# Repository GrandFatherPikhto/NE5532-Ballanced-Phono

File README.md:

# NE5532 Balanced Phono Preamplifier

[Русская версия](README_ru.md)

A stereo moving-magnet phono preamplifier for the Audio-Technica AT-3600L,
using NE5532 operational amplifiers and RIAA playback equalization.
The main design has balanced inputs from floating cartridge coils and
conventional, ground-referenced line outputs. An earlier unbalanced design
is retained for comparison.

## Design

Each channel uses two input amplifiers with a shared gain-setting bridge,
followed by a differential amplifier with the 75 µs RIAA pole. The stereo
design uses three dual NE5532 packages and a ±12 V supply.

| Parameter | Nominal design |
| --- | --- |
| Cartridge | Audio-Technica AT-3600L, moving magnet |
| Differential input load | 47 kΩ in the midband: 23.5 kΩ from each input to GND |
| Input coupling | 4.7 µF per leg |
| Input amplifier feedback | 90.9 kΩ in parallel with a series 10 kΩ / 31.5 nF branch |
| Gain bridge | 182 Ω in series with two back-to-back 1000 µF capacitors |
| Differential amplifier | Four 10 kΩ resistors and two matched 7.5 nF capacitors per channel |
| Line output | 100 Ω, series 4.7 µF, 100 kΩ to GND |
| Power | ±12 V, supplied through J3 |

The bridge capacitors have their negative terminals joined at a floating
midpoint. Their linear series equivalent is 500 µF. The L− and R− cartridge
connections remain separate from GND; cable shields and the tonearm ground
are separate connections.

With the nominal values in `scripts/config.toml` and an external 47 kΩ load,
the ideal model gives 100.723 V/V (40.063 dB) at 1 kHz. A 4 mV RMS
differential input gives approximately 0.403 V RMS at that frequency.
The ideal RIAA deviation, normalized at 1 kHz, is −0.0683 to +0.0018 dB
over 20 Hz–20 kHz.

## Project status and model limits

PCB routing is complete; hardware measurements are still pending. Component
ratings and purchased parts must be checked before assembly.
The separate LM317/LM337 power supply is documented in
LaTeX; the KiCad preamplifier schematic receives regulated ±12 V and does
not include that regulator circuit.

The Python tools compare an analytical transfer function with a nodal model
and estimate the effect of a single-pole op-amp model. These calculations
do not establish measured noise, THD, stability, overload margin or CMRR.
They omit cartridge impedance, cable capacitance, component tolerances,
capacitor leakage and nonlinearity, and PCB parasitics.

## Files

| Path | Contents |
| --- | --- |
| `PreAmp.kicad_pro`, `PreAmp.kicad_sch` | Main KiCad project and schematic |
| `channel.kicad_sch`, `arm.kicad_sch`, `power.kicad_sch` | Active hierarchical sheets; earlier variants are kept separately |
| `PreAmp.net` | Exported netlist snapshot; may lag behind the schematic |
| `out/` | Condensed netlists, BOM and audit snapshots for quick inspection |
| `scripts/` | Python models, plotting tools, dependencies and `config.toml` |
| `docs/latex/` | Circuit documents, shared LaTeX support files and PDF snapshots |
| `docs/images/` | Published simulation plots in PNG, SVG and PDF |
| [docs/simulation/ngspice-2026-11-28/](docs/simulation/ngspice-2026-11-28/) | Archived ngspice results, source netlists and run parameters |
| [docs/PHONO_GUIDE.pdf](docs/PHONO_GUIDE.pdf) | Detailed design guide in Russian; source: [PHONO_GUIDE.tex](docs/PHONO_GUIDE.tex) |
| [docs/POWER.md](docs/POWER.md) | Preliminary transformer notes; actual voltages and phasing require verification |
| `docs/scheme/` | Reference scans for the Melodiya-103 player |
| `build/` | Generated calculations, plots, check reports and document builds; ignored by Git |

Use the current KiCad schematic to establish connectivity and
`scripts/config.toml` for the calculation parameters. KiCad, TOML and LaTeX
are maintained independently; changing one does not update the others.
Historical filenames containing `ballanced` and `ad3600l` are preserved.

## Run the calculations

Use Python 3.11 or newer. Run these commands from the repository root:

```sh
python3 -m venv scripts/.venv
scripts/.venv/bin/python -m pip install -e scripts
scripts/.venv/bin/python scripts/calculate_balanced_riaa.py
scripts/.venv/bin/python scripts/calculate_unbalanced_riaa.py
scripts/.venv/bin/python scripts/render_phono_guide.py
```

Dependencies are declared in `scripts/pyproject.toml`. Both calculation
scripts load `scripts/config.toml` by default and write CSV, JSON, PNG and
PDF results to `build/balanced_riaa/`, including the unbalanced results.
The guide renderer writes to `build/phono_guide/`.

To choose a configuration and output directory explicitly:

```sh
scripts/.venv/bin/python scripts/calculate_balanced_riaa.py \
  --config scripts/config.toml --output-dir build/check
```

## Run the QSPICE simulation on Windows

Install Python 3.11 or later, KiCad with `kicad-cli.exe`, and QSPICE with
`QSPICE64.exe`. Open PowerShell in the project root and run:

```powershell
python -m pip install -e scripts
python scripts/simulate_qspice.py
```

Install the Python dependencies once per environment. Save your changes in
KiCad before each run. The script exports the saved hierarchical schematic
`PreAmp.kicad_sch` to fresh XML and builds the SPICE netlists from that export.
Component values and connections come from this XML, so there is no need to
regenerate `PreAmp.net`.

The [`[qspice]` section of the TOML file](scripts/config.toml) controls the
output directory, report and plot generation, and optional overrides for
frequency range, point count, RIAA reference frequency, and external load.
Set `kicad_cli` and `qspice64` there if automatic detection misses your
installation, or pass `--kicad-cli` and `--qspice64` on the command line.
Use `--config path/to/config.toml` for a separate set of settings. Setting
`write_plots = false` allows running without Matplotlib.

Each run prints the path to its results directory (by default,
`build/qspice/run-*/`). Open `report.md` for gain at the reference frequency
and the RIAA error extrema and their frequencies. Open `response.png` or
`response.svg` for both channels' gain, phase, and RIAA error. The directory
also contains per-channel CSV, CIR and QRAW files and the KiCad XML export.

The script generates a linear, single-pole NE5532 approximation from the
existing `[opamp]` settings (default open-loop gain 100,000 and GBW 12 MHz).
It estimates gain and phase with an ideal differential source. Cartridge
impedance, cable capacitance, noise, and output clipping are outside this
model.

## Run ngspice independently

Install ngspice and KiCad CLI, then run from the project root:

```sh
python scripts/simulate_ngspice.py
```

This exports the saved KiCad schematic and runs both channels without a
previous QSPICE run. On Linux and Windows, native ngspice is used when found
on `PATH`. On Windows, `backend = "auto"` falls back to ngspice inside WSL;
KiCad CLI still runs on the host. Use `--backend native` or `--backend wsl`
to select explicitly.

The [`[ngspice]` section](scripts/config.toml) controls the backend, output
directory, report/plot switches, timeout and optional overrides of the
`[analysis]` frequency range, reference frequency, load and point count.
`points` controls the target logarithmic sweep density; the exact sample
count can differ because SPICE uses an integer number of points per decade.
Executable paths can be set with `ngspice`/`kicad_cli` or the CLI options
`--ngspice`/`--kicad-cli`. `wsl_distro` or `--distro` selects the WSL distribution.
CLI options take priority. Paths in TOML are relative to the project root;
an executable's bare name is looked up on `PATH`.

```sh
python scripts/simulate_ngspice.py --config scripts/config.toml --backend native
python scripts/compare_ngspice.py build/qspice/run-example --backend native
```

Results go to a new `build/ngspice/run-*/` directory: per-channel CSV
(gain, phase and RIAA error), DAT (frequency and complex voltage), CIR and
logs, plus the KiCad XML, original configuration and effective run metadata.
With `write_report = true`, `report.md` and `report.json` contain the gain
and RIAA extrema; with `write_plots = true`, `response.png` and `response.svg`
show gain, phase and RIAA error for both channels. Disable plots to run
without Matplotlib. Comparison mode retains its per-channel comparison CSV
and uses the same ngspice backend settings without modifying the QSPICE decks.

Both simulators use the same linear one-pole op-amp approximation described
above. These plots do not predict noise, distortion, overload or real-device
stability.

## Published ngspice results — 28 November 2026

The snapshot below comes from `build/ngspice/run-_ttt3q4u`, using ngspice
45.2 with the KiCad-exported component values and connections. The input is
an ideal differential source; the external load is 47 kΩ per channel.
The sweep covers 20 Hz–20 kHz with 1003 samples per channel. RIAA deviation
is normalized at 1 kHz. The one-pole op-amp model uses A₀ = 100,000 and
GBW = 12 MHz.

| Quantity | Left | Right |
| --- | ---: | ---: |
| Gain at 1 kHz, V/V | 100.23888 | 100.23888 |
| Gain at 1 kHz, dB | 40.02072 | 40.02072 |
| Minimum RIAA deviation, dB | −0.11942 at 20 kHz | −0.11942 at 20 kHz |
| Maximum RIAA deviation, dB | +0.00131 at 382.36 Hz | +0.00131 at 382.36 Hz |

The top panel shows the intended RIAA playback response; the falling gain
with frequency is part of the equalization. The middle panel shows signal
phase, and the bottom panel shows deviation from the RIAA reference after
removing the gain difference at 1 kHz. For a 4 mV RMS differential input,
the modeled output at 1 kHz is approximately 0.401 V RMS.

The L/R curves overlap because the simulation uses matched nominal parts
and identical op-amp parameters, without component tolerances. This does
not establish real channel matching or CMRR. The finite open-loop gain
makes this result slightly different from the ideal-op-amp calculation
above. The KiCad snapshot also uses 23.51 kΩ and 90.91 kΩ resistor sums,
where the analytical configuration uses rounded 23.5 kΩ and 90.9 kΩ values.
Cartridge/cable impedance, PCB parasitics, noise, distortion, clipping and
real-device stability are outside this model.

The [archived data and reproduction notes](docs/simulation/ngspice-2026-11-28/README.md)
include CSV/DAT results, SPICE decks, the KiCad XML, configuration and run
metadata. The [balanced circuit PDF](docs/latex/ne5532_ad3600l_ballanced.pdf)
and [design guide](docs/PHONO_GUIDE.pdf) include the same results and comments.

## Build the documents

Install XeLaTeX, latexmk and the TeX packages used by the documents, including
TikZ/PGFPlots, fontspec and polyglossia. The shared preamble requires
Times New Roman, Arial and Courier New. A local circuitikz style is included.
Generate the calculations and guide figures above before building.

From the repository root:

```sh
TEXINPUTS=.:./docs/latex//: latexmk -xelatex -interaction=nonstopmode \
  -halt-on-error -outdir=build/latex docs/latex/ne5532_ad3600l_ballanced.tex
TEXINPUTS=.:./docs/latex//: latexmk -xelatex -interaction=nonstopmode \
  -halt-on-error -outdir=build/latex docs/latex/ne5532_at3600l.tex
TEXINPUTS=.:./docs/latex//: latexmk -xelatex -interaction=nonstopmode \
  -halt-on-error -outdir=build/latex docs/latex/analog_power_lm317_lm337.tex
TEXINPUTS=.:./docs/latex//: latexmk -xelatex -interaction=nonstopmode \
  -halt-on-error -outdir=build/phono_guide docs/PHONO_GUIDE.tex
```

The trailing colon in `TEXINPUTS` preserves the system TeX search path.
New PDFs remain in `build/`; checked-in PDF snapshots under `docs/` are
updated manually. Some existing documents contain commands from an earlier
directory layout; use the commands in this README for the current layout.

## Check the KiCad schematic

The project was last checked with KiCad 10.0.8. Save changes in the editor
before exporting or running ERC:

```sh
mkdir -p build/review
kicad-cli sch erc --format json --severity-all \
  --output build/review/erc.json PreAmp.kicad_sch
kicad-cli sch export netlist --format kicadsexpr \
  --output build/review/PreAmp.net PreAmp.kicad_sch
```

ERC checks enabled electrical rules. It does not validate component ratings,
footprint dimensions, equalization accuracy, stability or PCB layout.

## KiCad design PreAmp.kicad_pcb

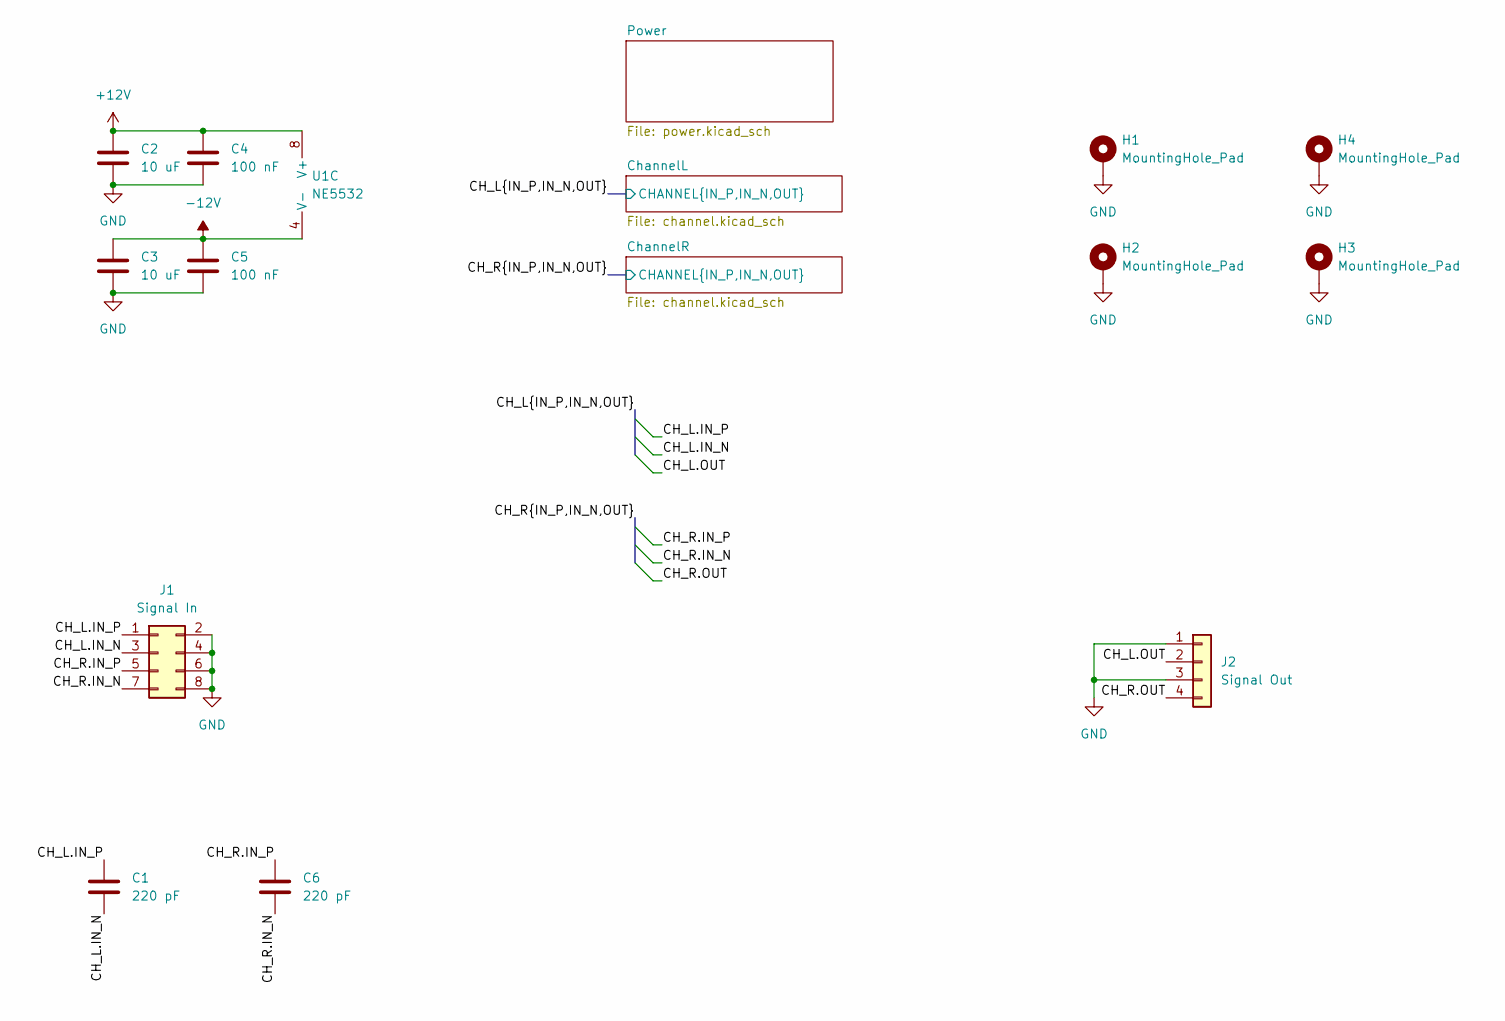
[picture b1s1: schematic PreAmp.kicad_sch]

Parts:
C1, C6: 220 pF; C_0603_1608Metric_Pad1.08x0.95mm_HandSolder
C2, C3: 10 uF; C_0603_1608Metric_Pad1.08x0.95mm_HandSolder
C4, C5: 100 nF; C_0402_1005Metric_Pad0.74x0.62mm_HandSolder
H1, H2, H3, H4: MountingHole_Pad; MountingHole_3.2mm_M3_DIN965_Pad
J1: Signal In; IDC-Header_2x04_P2.54mm_Vertical
J2: Signal Out; JST_XH_B4B-XH-A_1x04_P2.50mm_Vertical
U1: NE5532; SOIC-8_3.9x4.9mm_P1.27mm

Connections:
+12V: C2.1, C4.1, U1.8 (V+); also elsewhere on the board
-12V: C3.1, C5.1, U1.4 (V-); also elsewhere on the board
/CH_L.IN_N: C1.2, J1.3; also elsewhere on the board
/CH_L.IN_P: C1.1, J1.1; also elsewhere on the board
/CH_L.OUT: J2.2; also elsewhere on the board
/CH_R.IN_N: C6.2, J1.7; also elsewhere on the board
/CH_R.IN_P: C6.1, J1.5; also elsewhere on the board
/CH_R.OUT: J2.4; also elsewhere on the board
/ChannelR/DIFF_IN_N: U1.6 (-); also elsewhere on the board
/ChannelR/DIFF_IN_P: U1.5 (+); also elsewhere on the board
/ChannelR/DIFF_OUT: U1.7; also elsewhere on the board
GND: C2.2, C3.2, C4.2, C5.2, H1.1 (1_1), H2.1 (1_1), H3.1 (1_1), H4.1 (1_1), J1.2, J1.4, J1.6, J1.8, J2.1, J2.3; also elsewhere on the board

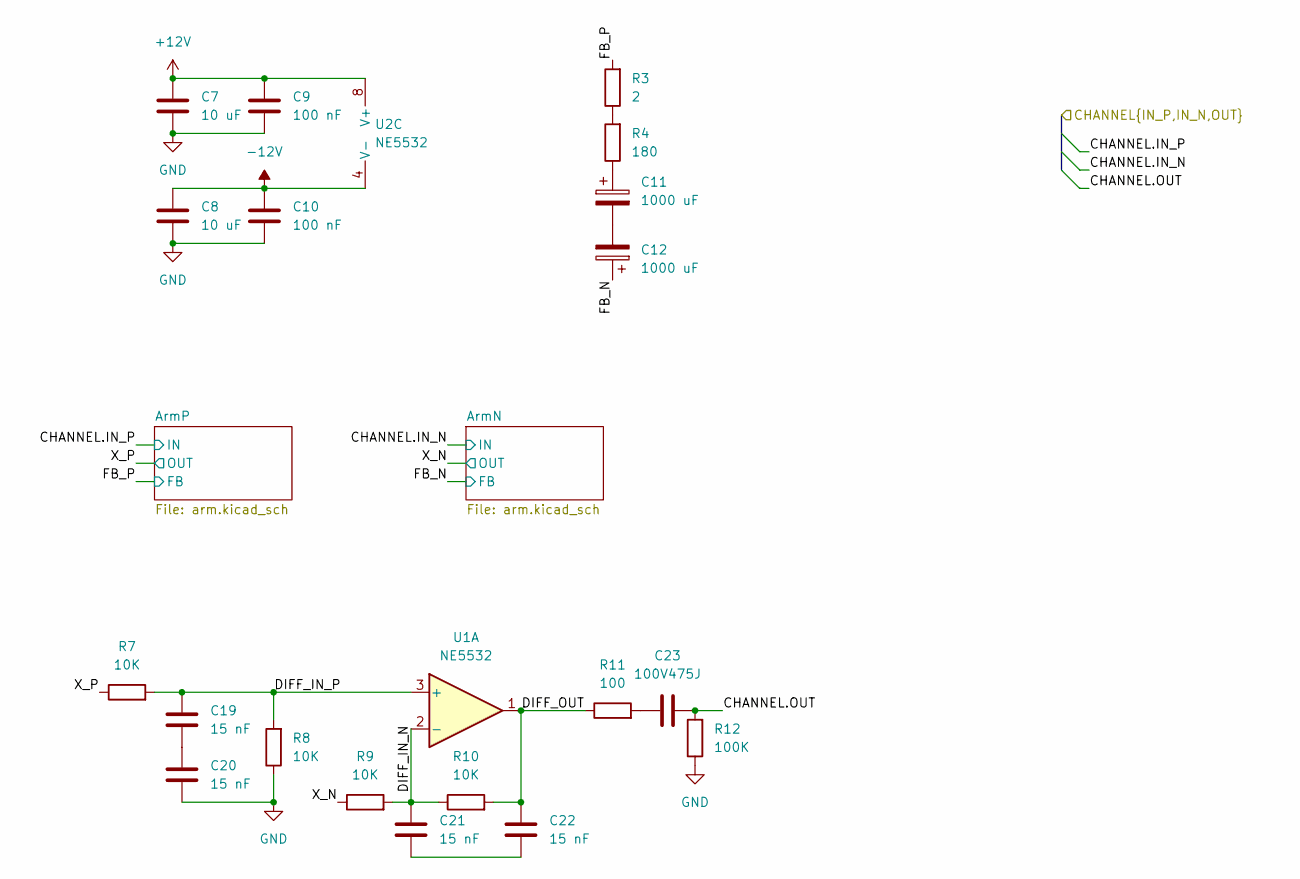
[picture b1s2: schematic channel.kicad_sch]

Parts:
C7, C8: 10 uF; C_0603_1608Metric_Pad1.08x0.95mm_HandSolder
C9, C10: 100 nF; C_0402_1005Metric_Pad0.74x0.62mm_HandSolder
C11, C12: 1000 uF; CP_Radial_D10.0mm_P5.00mm
C19, C20, C21, C22: 15 nF; C_0603_1608Metric_Pad1.08x0.95mm_HandSolder
C23: 100V475J; C_Rect_L18.0mm_W8.0mm_P15.00mm_FKS3_FKP3
R3: 2; R_0603_1608Metric_Pad0.98x0.95mm_HandSolder
R4: 180; R_0603_1608Metric_Pad0.98x0.95mm_HandSolder
R7, R8, R9, R10: 10K; R_0402_1005Metric_Pad0.72x0.64mm_HandSolder
R11: 100; R_0402_1005Metric_Pad0.72x0.64mm_HandSolder
R12: 100K; R_0402_1005Metric_Pad0.72x0.64mm_HandSolder
U1, U2: NE5532; SOIC-8_3.9x4.9mm_P1.27mm

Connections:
+12V: C7.1, C9.1, U2.8 (V+); also elsewhere on the board
-12V: C8.1, C10.1, U2.4 (V-); also elsewhere on the board
/CH_L.OUT: C23.2, R12.2; also elsewhere on the board
/ChannelL/ArmN/IN_AC: U2.5 (+); also elsewhere on the board
/ChannelL/DIFF_IN_N: C21.2, R9.2, R10.1, U1.2 (-)
/ChannelL/DIFF_IN_P: C19.1, R7.2, R8.2, U1.3 (+)
/ChannelL/DIFF_OUT: C22.1, R10.2, R11.1, U1.1
/ChannelL/FB_N: C12.1, U2.6 (-); also elsewhere on the board
/ChannelL/FB_P: R3.2; also elsewhere on the board
/ChannelL/X_N: R9.1, U2.7; also elsewhere on the board
/ChannelL/X_P: R7.1; also elsewhere on the board
/ChannelR/DIFF_IN_N: U1.6 (-); also elsewhere on the board
/ChannelR/DIFF_IN_P: U1.5 (+); also elsewhere on the board
/ChannelR/DIFF_OUT: U1.7; also elsewhere on the board
GND: C7.2, C8.2, C9.2, C10.2, C20.2, R8.1, R12.1; also elsewhere on the board
unnamed: C11.1, R4.1
unnamed: C11.2, C12.2
unnamed: C19.2, C20.1
unnamed: C21.1, C22.2
unnamed: C23.1, R11.2
unnamed: R3.1, R4.2

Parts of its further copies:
C13, C14: 10 uF; C_0603_1608Metric_Pad1.08x0.95mm_HandSolder
C15, C16: 100 nF; C_0402_1005Metric_Pad0.74x0.62mm_HandSolder
C17, C18: 1000 uF; CP_Radial_D10.0mm_P5.00mm
C24, C25, C26, C27: 15 nF; C_0603_1608Metric_Pad1.08x0.95mm_HandSolder
C28: 100V475J; C_Rect_L18.0mm_W8.0mm_P15.00mm_FKS3_FKP3
R5: 2; R_0603_1608Metric_Pad0.98x0.95mm_HandSolder
R6: 180; R_0603_1608Metric_Pad0.98x0.95mm_HandSolder
R13, R14, R15, R16: 10K; R_0402_1005Metric_Pad0.72x0.64mm_HandSolder
R17: 100; R_0402_1005Metric_Pad0.72x0.64mm_HandSolder
R18: 100K; R_0402_1005Metric_Pad0.72x0.64mm_HandSolder
U3: NE5532; SOIC-8_3.9x4.9mm_P1.27mm

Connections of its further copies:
+12V: C13.1, C15.1, U3.8 (V+); also elsewhere on the board
-12V: C14.1, C16.1, U3.4 (V-); also elsewhere on the board
/CH_R.OUT: C28.2, R18.2; also elsewhere on the board
/ChannelR/ArmN/IN_AC: U3.5 (+); also elsewhere on the board
/ChannelR/ArmP/IN_AC: U3.3 (+); also elsewhere on the board
/ChannelR/DIFF_IN_N: C26.2, R15.2, R16.1; also elsewhere on the board
/ChannelR/DIFF_IN_P: C24.1, R13.2, R14.2; also elsewhere on the board
/ChannelR/DIFF_OUT: C27.1, R16.2, R17.1; also elsewhere on the board
/ChannelR/FB_N: C18.1, U3.6 (-); also elsewhere on the board
/ChannelR/FB_P: R5.2, U3.2 (-); also elsewhere on the board
/ChannelR/X_N: R15.1, U3.7; also elsewhere on the board
/ChannelR/X_P: R13.1, U3.1; also elsewhere on the board
GND: C13.2, C14.2, C15.2, C16.2, C25.2, R14.1, R18.1; also elsewhere on the board
unnamed: C17.1, R6.1
unnamed: C17.2, C18.2
unnamed: C24.2, C25.1
unnamed: C26.1, C27.2
unnamed: C28.1, R17.2
unnamed: R5.1, R6.2

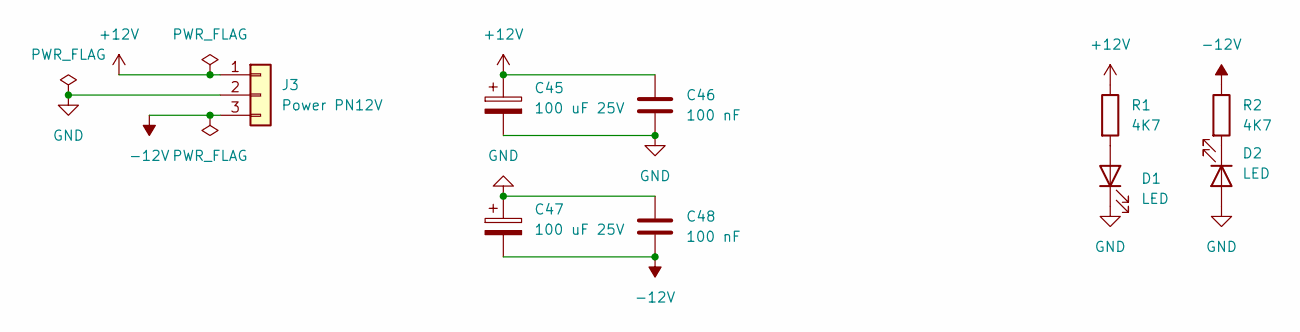
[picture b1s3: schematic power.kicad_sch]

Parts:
C45, C47: 100 uF 25V; CP_Radial_D5.0mm_P2.50mm
C46, C48: 100 nF; C_0603_1608Metric_Pad1.08x0.95mm_HandSolder
D1, D2: LED; LED_0805_2012Metric_Pad1.15x1.40mm_HandSolder
J3: Power PN12V; JST_XH_B3B-XH-A_1x03_P2.50mm_Vertical
R1, R2: 4K7; R_0603_1608Metric_Pad0.98x0.95mm_HandSolder

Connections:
+12V: C45.1, C46.1, J3.1, R1.1; also elsewhere on the board
-12V: C47.2, C48.2, J3.3, R2.1; also elsewhere on the board
GND: C45.2, C46.2, C47.1, C48.1, D1.1 (K), D2.2 (A), J3.2; also elsewhere on the board
unnamed: D1.2 (A), R1.2
unnamed: D2.1 (K), R2.2

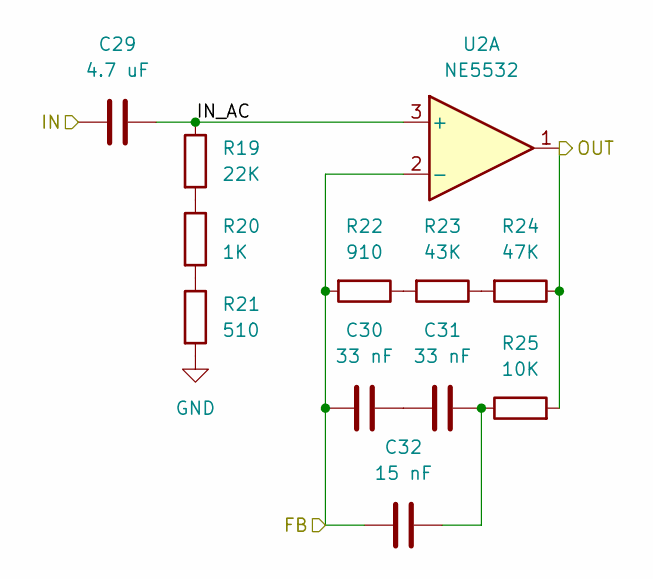
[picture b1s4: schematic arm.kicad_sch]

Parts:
C29: 4.7 uF; C_Rect_L18.0mm_W8.0mm_P15.00mm_FKS3_FKP3
C30, C31: 33 nF; C_0603_1608Metric_Pad1.08x0.95mm_HandSolder
C32: 15 nF; C_0603_1608Metric_Pad1.08x0.95mm_HandSolder
R19: 22K; R_0402_1005Metric_Pad0.72x0.64mm_HandSolder
R20: 1K; R_0402_1005Metric_Pad0.72x0.64mm_HandSolder
R21: 510; R_0402_1005Metric_Pad0.72x0.64mm_HandSolder
R22: 910; R_0402_1005Metric_Pad0.72x0.64mm_HandSolder
R23: 43K; R_0402_1005Metric_Pad0.72x0.64mm_HandSolder
R24: 47K; R_0402_1005Metric_Pad0.72x0.64mm_HandSolder
R25: 10K; R_0402_1005Metric_Pad0.72x0.64mm_HandSolder
U2: NE5532; SOIC-8_3.9x4.9mm_P1.27mm

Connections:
/CH_L.IN_P: C29.1; also elsewhere on the board
/ChannelL/ArmN/IN_AC: U2.5 (+); also elsewhere on the board
/ChannelL/ArmP/IN_AC: C29.2, R19.1, U2.3 (+)
/ChannelL/FB_N: U2.6 (-); also elsewhere on the board
/ChannelL/FB_P: C30.1, C32.1, R22.2, U2.2 (-); also elsewhere on the board
/ChannelL/X_N: U2.7; also elsewhere on the board
/ChannelL/X_P: R24.1, R25.2, U2.1; also elsewhere on the board
GND: R21.2; also elsewhere on the board
unnamed: C30.2, C31.1
unnamed: C31.2, C32.2, R25.1
unnamed: R19.2, R20.1
unnamed: R20.2, R21.1
unnamed: R22.1, R23.2
unnamed: R23.1, R24.2

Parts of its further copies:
C33, C37, C41: 4.7 uF; C_Rect_L18.0mm_W8.0mm_P15.00mm_FKS3_FKP3
C34, C35, C38, C39, C42, C43: 33 nF; C_0603_1608Metric_Pad1.08x0.95mm_HandSolder
C36, C40, C44: 15 nF; C_0603_1608Metric_Pad1.08x0.95mm_HandSolder
R26, R33, R40: 22K; R_0402_1005Metric_Pad0.72x0.64mm_HandSolder
R27, R34, R41: 1K; R_0402_1005Metric_Pad0.72x0.64mm_HandSolder
R28, R35, R42: 510; R_0402_1005Metric_Pad0.72x0.64mm_HandSolder
R29, R36, R43: 910; R_0402_1005Metric_Pad0.72x0.64mm_HandSolder
R30, R37, R44: 43K; R_0402_1005Metric_Pad0.72x0.64mm_HandSolder
R31, R38, R45: 47K; R_0402_1005Metric_Pad0.72x0.64mm_HandSolder
R32, R39, R46: 10K; R_0402_1005Metric_Pad0.72x0.64mm_HandSolder
U3: NE5532; SOIC-8_3.9x4.9mm_P1.27mm

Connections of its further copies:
+12V: U3.8 (V+); also elsewhere on the board
-12V: U3.4 (V-); also elsewhere on the board
/CH_L.IN_N: C33.1; also elsewhere on the board
/CH_R.IN_N: C41.1; also elsewhere on the board
/CH_R.IN_P: C37.1; also elsewhere on the board
/ChannelL/ArmN/IN_AC: C33.2, R26.1; also elsewhere on the board
/ChannelL/FB_N: C34.1, C36.1, R29.2; also elsewhere on the board
/ChannelL/X_N: R31.1, R32.2; also elsewhere on the board
/ChannelR/ArmN/IN_AC: C41.2, R40.1, U3.5 (+)
/ChannelR/ArmP/IN_AC: C37.2, R33.1, U3.3 (+)
/ChannelR/FB_N: C42.1, C44.1, R43.2, U3.6 (-); also elsewhere on the board
/ChannelR/FB_P: C38.1, C40.1, R36.2, U3.2 (-); also elsewhere on the board
/ChannelR/X_N: R45.1, R46.2, U3.7; also elsewhere on the board
/ChannelR/X_P: R38.1, R39.2, U3.1; also elsewhere on the board
GND: R28.2, R35.2, R42.2; also elsewhere on the board
unnamed: C34.2, C35.1
unnamed: C35.2, C36.2, R32.1
unnamed: C38.2, C39.1
unnamed: C39.2, C40.2, R39.1
unnamed: C42.2, C43.1
unnamed: C43.2, C44.2, R46.1
unnamed: R26.2, R27.1
unnamed: R27.2, R28.1
unnamed: R29.1, R30.2
unnamed: R30.1, R31.2
unnamed: R33.2, R34.1
unnamed: R34.2, R35.1
unnamed: R36.1, R37.2
unnamed: R37.1, R38.2
unnamed: R40.2, R41.1
unnamed: R41.2, R42.1
unnamed: R43.1, R44.2
unnamed: R44.1, R45.2

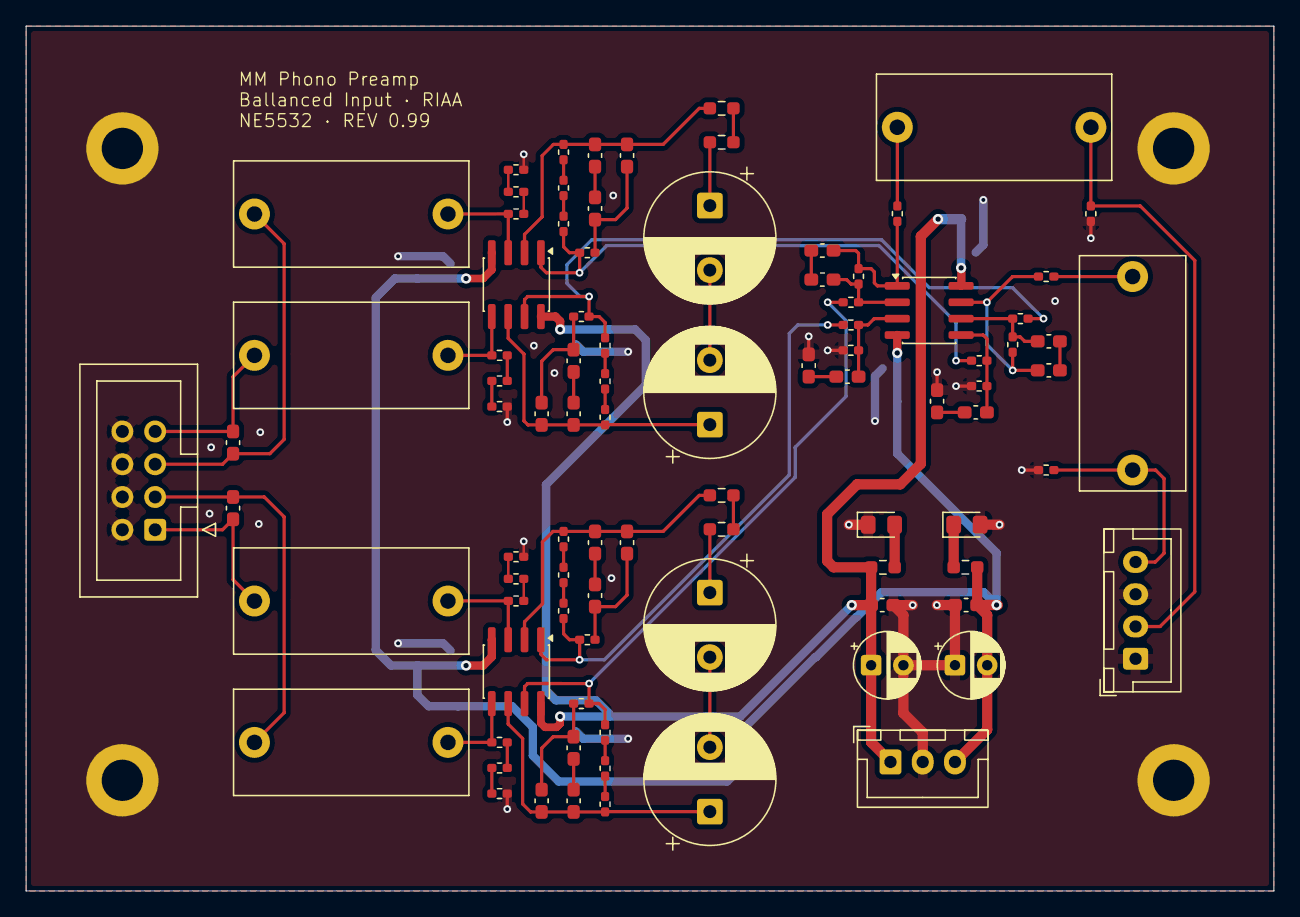
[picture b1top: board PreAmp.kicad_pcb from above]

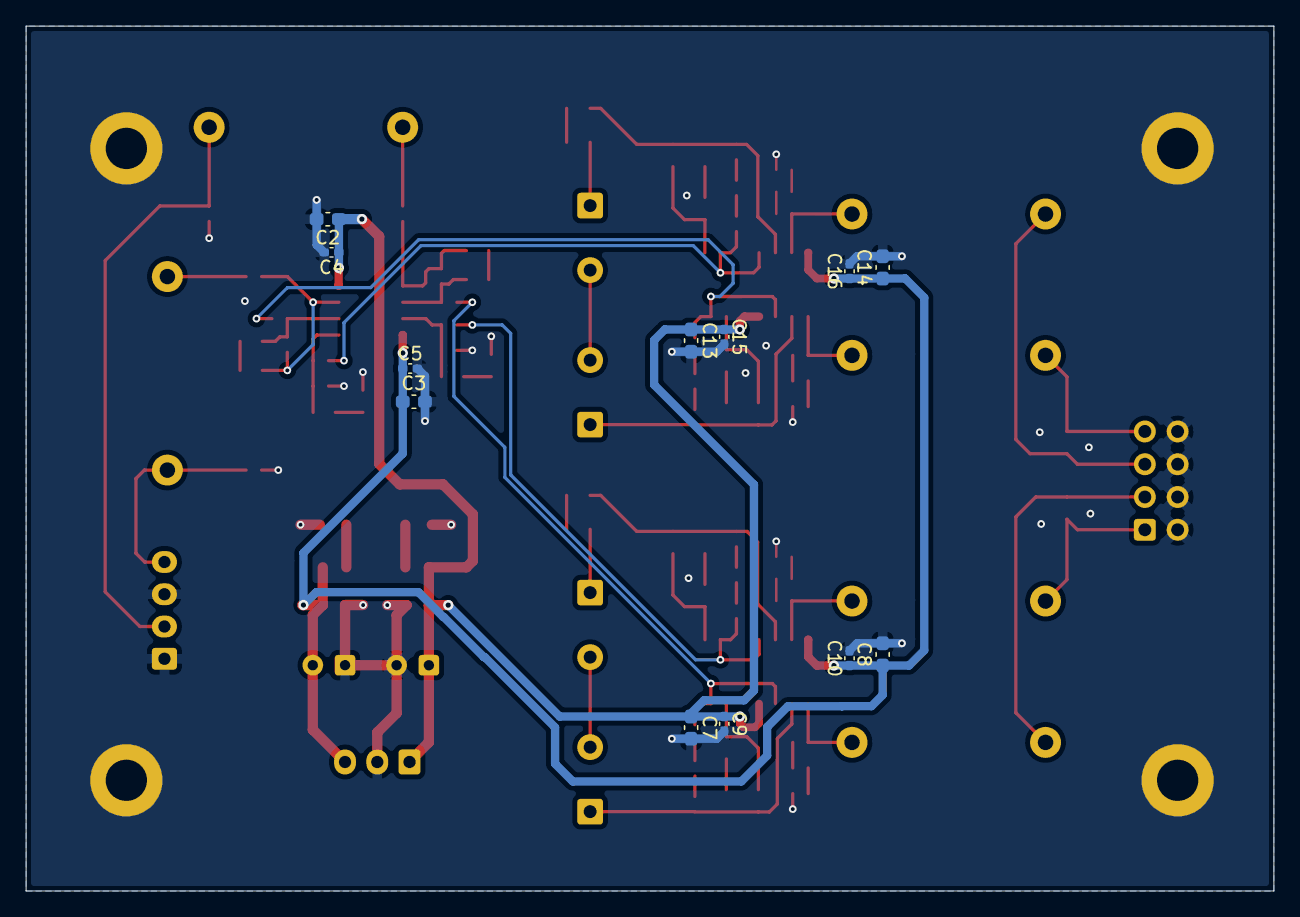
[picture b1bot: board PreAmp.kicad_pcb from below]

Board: 2 copper layers, 96.7 x 67.0 mm, 106 parts (12 on the bottom side), 65 nets.
